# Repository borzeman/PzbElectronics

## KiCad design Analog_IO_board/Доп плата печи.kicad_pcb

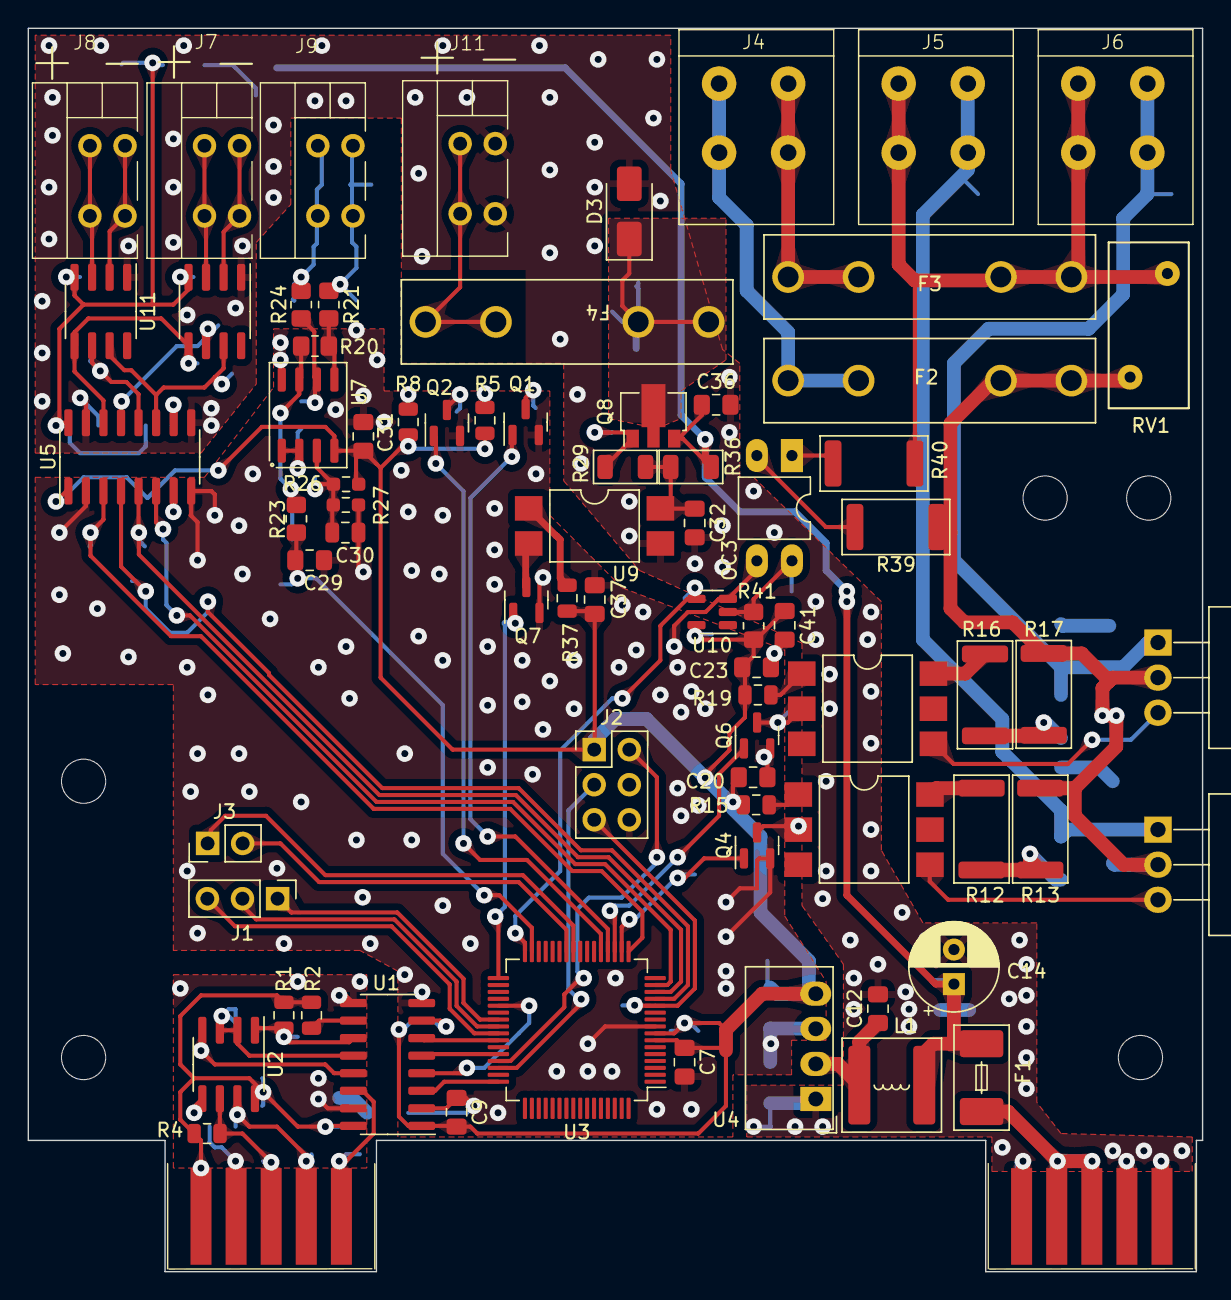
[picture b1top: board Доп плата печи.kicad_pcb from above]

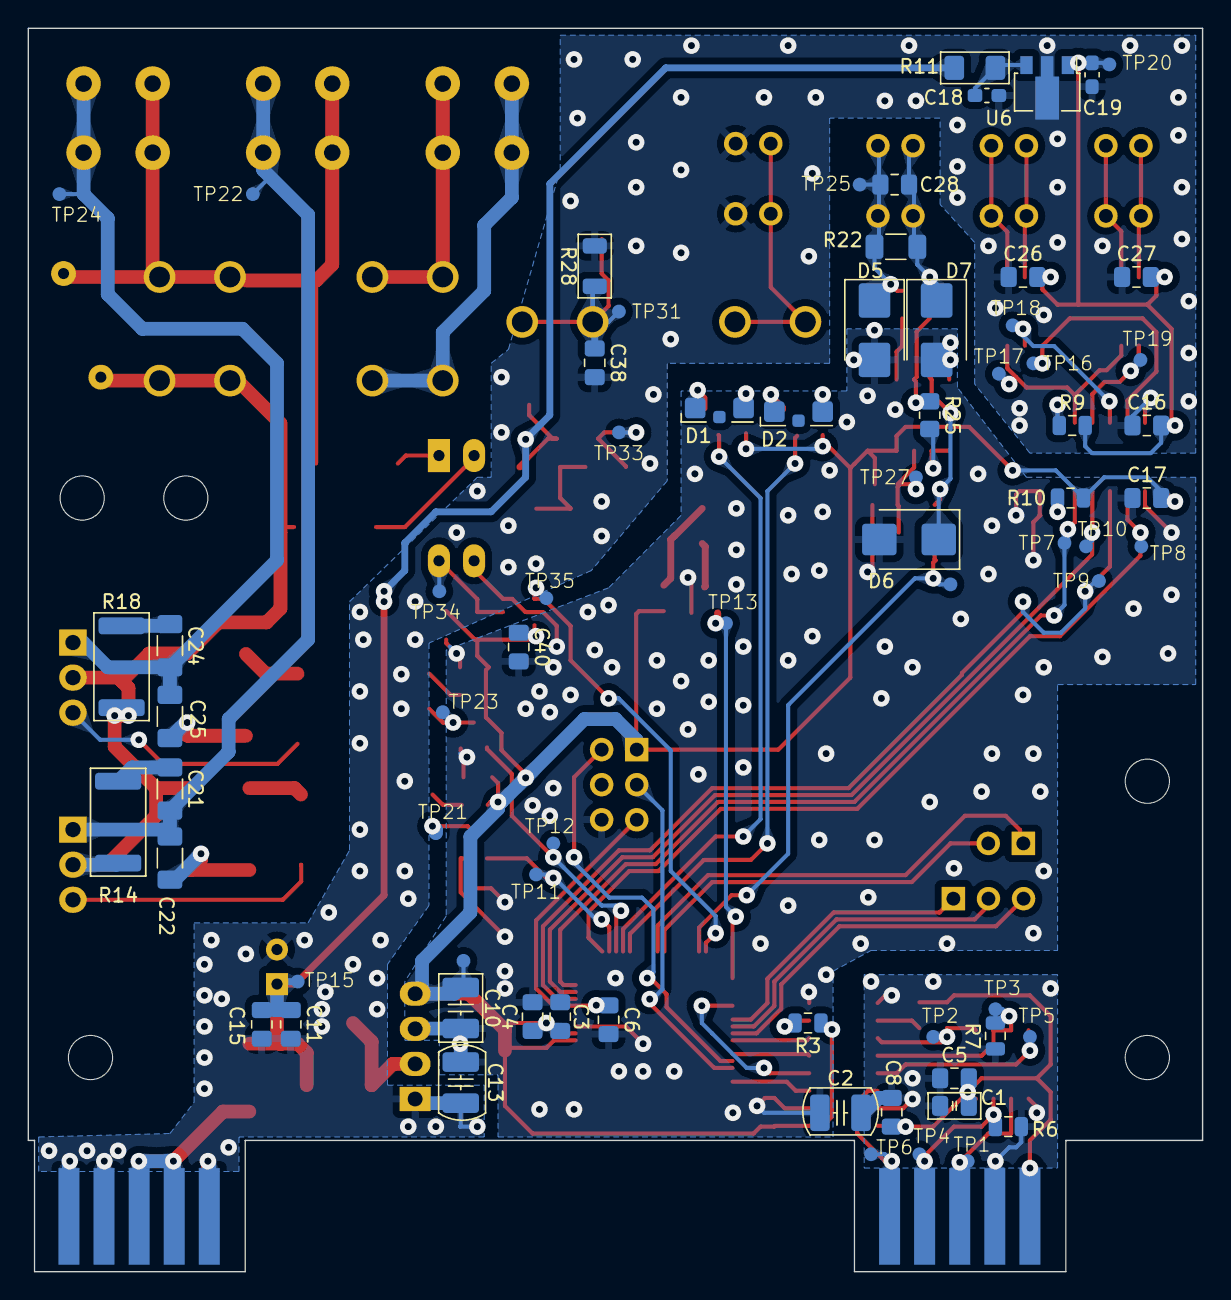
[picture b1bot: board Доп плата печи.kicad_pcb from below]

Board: 2 copper layers, 85.0 x 90.0 mm, 153 parts (72 on the bottom side), 89 nets.

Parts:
C1: 1uF 100V 0805; C_0805_2012Metric_Pad1.18x1.45mm_HandSolder
C2, C13: 270 pf X7R 1206 2000v 202R18W271KW4E; C_1210_3225Metric_Pad1.42x2.65mm
C3, C5, C6, C7, C8, C9, C15, C16, C17, C20, C23, C26, C27, C29, C32, C36, C37, C38: 0,1uF 100V 0805; C_0805_2012Metric_Pad1.18x1.45mm_HandSolder
C4, C11, C12: 4,7uF 50V 0805; C_0805_2012Metric_Pad1.18x1.45mm_HandSolder
C10: 10uF 50V 1210 GRM32ER71H106K; C_1210_3225Metric_Pad1.42x2.65mm_HandSolder
C14: 47uF 63V D6.3 H11; CP_Radial_D6.3mm_P2.50mm
C18: 0,33uF 50V 0603; C_0603_1608Metric_Pad1.08x0.95mm_HandSolder
C19: 0,1uF 50V 0603; C_0603_1608Metric_Pad1.08x0.95mm_HandSolder
C21, C22, C24, C25: 0,01uF 600V 1206 (GRM31BR72J103KW01L); C_1206_3216Metric_Pad1.33x1.80mm_HandSolder
C28, C31: 1uF 50V 0805; C_0805_2012Metric_Pad1.18x1.45mm_HandSolder
C30: 10uF 16V 0805; C_0805_2012Metric
C40, C41: 0,1uF 50V 0805; C_0805_2012Metric_Pad1.18x1.45mm_HandSolder
D1, D2: KPA-3010CGCK; LED_Kingbright_KPA-3010_3x2x1mm
D3: STPS2H100A (D_SMA); D_SMA
D5, D6, D7: SMBJ3V3-E3/52 (D_SMB); D_SMB
F1: 045201.5MRL; Fuse_Littelfuse-NANO2-451_453
F2, F3: Fuse 5A ZH266 (2 клипсы); Fuseholder_100_series_5x20mm_D1,5
F4: Fuse 0,16A 5x20 and ZH266 (2 клипсы); Fuseholder_100_series_5x20mm_D1,5
H1, H2, H3, H4, H5: MountingHole; MountingHole_3.2mm_M3
J1: DebugUSART (PinHeader_01x03_P2.54mm); PinHeader_1x03_P2.54mm_Vertical
J2: Prog (PinHeader_2x03_P2.54mm); PinHeader_2x03_P2.54mm_Vertical
J3: Debug GPIO (PinHeader_01x02_P2.54mm); PinHeader_1x02_P2.54mm_Vertical
J4, J5, J6: DG245-5.0-02P
J7, J8, J9, J11: DG141R-02
L1: 6,8uH 3,5A ETQP3M6R8KVP; L_Bourns-SRN6028
OC1, OC2: MOC3023SM (SMDIP-6); SMDIP-6_W9.53mm
OC3: FOD814 (DIP-4); DIP-4_W7.62mm_LongPads
Q1, Q2, Q4, Q6, Q7: DTC114ECA (SOT-23); SOT-23
Q3, Q5: BT136X-800E TO-220; TO-220-3_Horizontal_TabDown
Q8: BCX53-16 (SOT-89-3); SOT-89-3
R1, R7: 0805-10 кОм±5%-0,125 Вт; R_0805_2012Metric
R2, R3, R9, R10: 0805-4,7 кОм±5%-0,125 Вт; R_0805_2012Metric
R4, R6: 0805-560 Ом±5%-0,125 Вт; R_0805_2012Metric
R5, R8: 0805-150 Ом±5%-0,125 Вт; R_0805_2012Metric
R11: 1206-620 Ом±5%-0,25 Вт; R_1206_3216Metric_Pad1.42x1.75mm_HandSolder
R12, R16: 2512-180 Ом±5%-1 Вт; R_2512_6332Metric
R13, R17: 2512-1 кОм±5%-1 Вт; R_2512_6332Metric
R14, R18: 2512-51 Ом±5%-1 Вт; R_2512_6332Metric
R15, R19, R37: 0805-200 Ом±5%-0,125 Вт; R_0805_2012Metric
R20, R21, R23, R24, R25: 0805-1 кОм±1%-0,125 Вт; R_0805_2012Metric_Pad1.20x1.40mm_HandSolder
R22: 1206-33 Ом±5%-0,25 Вт; R_1206_3216Metric_Pad1.30x1.75mm_HandSolder
R26, R27: 0603-1 кОм±1%-0,062 Вт; R_0603_1608Metric_Pad0.98x0.95mm_HandSolder
R28: 1206-10 кОм±5%-0,25 Вт; R_1206_3216Metric
R29, R36: 1206-20 кОм±5%-0,25 Вт; R_1206_3216Metric
R39, R40: 2512-51 кОм±5%-1 Вт; R_2512_6332Metric
R41: 0805-1 кОм±5%-0,125 Вт; R_0805_2012Metric_Pad1.20x1.40mm_HandSolder
RS1, RS2: SL-10 (L-KLS1-603C-10-S); Edge_Conn_KLS1-603-10
RV1: V10E250P; RV_Disc_D12mm_W5.8mm_P7.5mm
TP1, TP2, TP3, TP4, TP5, TP6, TP7, TP8, TP9, TP10, TP11, TP12, TP13, TP14, TP15, TP16, TP17, TP18, TP19, TP20, TP21, TP22, TP23, TP24, TP25, TP26, TP27, TP31, TP33, TP34, TP35: TestPoint; TestPoint_D1
U1, U5: PAI141M30 (SOIC-16); SOIC-16_3.9x9.9mm_P1.27mm
U2: ADM3485EARZ-REEL (SOIC-8); SOIC-8_3.9x4.9mm_P1.27mm
U3: STM32G070RBTx (LQFP-64); LQFP-64_10x10mm_P0.5mm
U4: AM1SS-2403SJZ; Converter_DCDC_Murata_MEE1SxxxxSC_THT
U6: L78L33 (SOT89); SOT-89-3
U7: LMV358IDT (SO-8); SO-8_3.9x4.9mm_P1.27mm
U8, U11: MAX31855KASA (SOIC-8); SOIC-8_3.9x4.9mm_P1.27mm
U9: LTV-817S-(С-D) (SMDIP-4); SMDIP-4_W9.53mm
U10: 74AHCT1G14GW,125 (SOT-23-5); SOT-23-5

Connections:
+3.3VA: C16.2, C19.1, C26.2, C27.2, R9.2, TP20.1, U5.16 (VDD2), U6.1 (OUT), U8.4 (V_CC), U11.4 (V_CC)
+3V3: C3.1, C4.1, C7.1, C9.2, C10.1, C17.2, C20.1, C23.1, C31.1, C37.1, C40.1, C41.1, J2.1, R3.1, R5.2, R8.1, R10.1, R15.1, R19.1, R26.1, R37.1, R41.2, TP14.1, U1.1 (VDD1), U3.7 (VREF+), U3.8 (VDD), U4.4 (OUT+), U5.1 (VDD1), U7.4 (V-), U10.5 (VCC)
+24V: C11.1, C14.1, C15.1, C36.1, F1.2, L1.1, Q8.3 (E), R11.2, R36.2, TP15.1
/+3.3VRS485: C1.2, C5.2, C8.2, R1.2, R2.2, R4.2, RS1.1, RS1.10, U1.16 (VDD2), U2.8 (VCC)
/AddSchems/ACIN_1: F2.2, Q3.2 (A2), Q5.2 (A2), R13.1, R14.2, R17.1, R18.2, R39.1, RV1.1
/AddSchems/ACIN_2: F3.1, J5.1, J6.1, R40.2, RV1.2
/AddSchems/ACOUT1: C21.2, C22.2, J5.2, Q3.1 (A1), TP22.1
/AddSchems/ACOUT2: C24.2, C25.2, J6.2, Q5.1 (A1), TP24.1
/AddSchems/CLK_out: TP16.1, U5.14 (VOA), U8.5 (SCK), U11.5 (SCK)
/AddSchems/CS1_out: TP18.1, U5.13 (VOB), U8.6 (~CS)
/AddSchems/CS2_out: TP19.1, U5.12 (VOC), U11.6 (~CS)
/AddSchems/MISO_out: TP17.1, U5.11 (VID), U8.7 (SO), U11.7 (SO)
/CLK: TP8.1, U3.17 (PA0), U5.3 (VIA)
/CS1: TP9.1, U3.13 (PC0), U5.4 (VIB)
/CS2: TP10.1, U3.14 (PC1), U5.5 (VIC)
/DE_USART_1: U1.5 (VIC), U3.44 (PA12/PA10)
/Detect_zero: TP35.1, U3.32 (PB12), U10.4
/GPIO1: J3.1, U3.25 (PC4)
/GPIO2: J3.2, U3.26 (PC5)
/MISO: TP7.1, U3.15 (PC2), U5.6 (VOD)
/NRST: C6.1, J2.5, U3.12 (NRST)
/RTS: RS1.5, RS1.6, TP6.1, U1.14 (VOA)
/RTS_cont: U1.3 (VIA), U3.48 (PC8)
/RX_USART_1: U1.6 (VOD), U3.42 (PA10/NC)
/Relay_ON: Q7.1 (B), TP13.1, U3.33 (PB13)
/SIM1_ON: Q4.1 (B), TP11.1, U3.18 (PA1)
/SIM2_ON: Q6.1 (B), TP12.1, U3.19 (PA2)
/SWCLK: J2.3, U3.46 (PA14)
/SWDIO: J2.2, U3.45 (PA13)
/TX_USART_1: U1.4 (VIB), U3.37 (PA9/NC)
/UART_DE: J1.1, U3.39 (PC7)
/UART_RX: J1.3, U3.41 (PD9)
/UART_TX: J1.2, U3.40 (PD8)
/U_Idet1: C29.1, R23.2, TP26.1, U3.31 (PB11)
GND1: C1.1, C2.1, C5.1, C8.1, R6.1, R7.1, RS1.2, RS1.9, U1.9 (GND2), U1.15 (GND2), U2.5 (GND)
GNDA: C11.2, C12.2, C13.1, C14.2, C15.2, C16.1, C18.2, C19.2, C26.1, C27.1, C32.2, C36.2, C38.2, D3.2 (A), J11.1, R28.2, RS2.1, RS2.4, RS2.5, RS2.6, RS2.7, RS2.10, U4.1 (IN-), U5.9 (GND2), U5.15 (GND2), U6.2 (GND), U8.1 (GND), U9.3, U11.1 (GND)
GNDD: C2.2, C3.2, C4.2, C6.2, C7.2, C9.1, C10.2, C13.2, C17.1, C20.2, C23.2, C29.2, C30.2, C31.2, C37.2, C40.2, C41.2, D5.2 (A), D6.2 (A), D7.2 (A), J2.6, OC3.3, Q1.2 (E), Q2.2 (E), Q4.2 (E), Q6.2 (E), Q7.2 (E), R27.2, U1.2 (GND1), U1.8 (GND1), U3.9 (VSS), U4.3 (OUT-), U5.2 (GND1), U5.8 (GND1), U7.8 (V+), U10.3 (GND)
unnamed: C21.1, R14.1
unnamed: C22.1, R12.1, R13.2
unnamed: C24.1, R18.1
unnamed: C25.1, R16.1, R17.2
unnamed: C32.1, R29.1, R36.1, U9.4
unnamed: D1.2 (A), R5.1
unnamed: D1.1 (K), Q1.3 (C)
unnamed: D2.2 (A), R8.2
unnamed: D2.1 (K), Q2.3 (C)
unnamed: C38.1, D3.1 (K), F4.1, Q8.2 (C), R28.1, TP31.1
unnamed: C28.1, D5.1 (K), J9.1, R21.1, R22.1, TP25.1
unnamed: D6.1 (K), R20.2, R23.1, U7.7
unnamed: C28.2, D7.1 (K), J9.2, R22.2, R24.1
unnamed: F2.1, J4.1
unnamed: F3.2, J4.2
unnamed: J7.1, U8.2 (T-)
unnamed: J7.2, U8.3 (T+)
unnamed: J8.1, U11.2 (T-)
unnamed: J8.2, U11.3 (T+)
unnamed: F4.2, J11.2
unnamed: OC1.1, R15.2
unnamed: OC1.6, R12.2
unnamed: OC2.1, R19.2
unnamed: OC2.6, R16.2
unnamed: OC3.1, R40.1
unnamed: OC3.2, R39.2
unnamed: OC3.4, R41.1, TP34.1, U10.2
unnamed: Q1.1 (B), U3.20 (PA3)
unnamed: Q2.1 (B), U3.21 (PA4)
unnamed: OC1.4, Q3.3 (G)
unnamed: OC1.2, Q4.3 (C), TP21.1
unnamed: OC2.4, Q5.3 (G)
unnamed: OC2.2, Q6.3 (C), TP23.1
unnamed: Q7.3 (C), U9.2
unnamed: Q8.1 (B), R29.2, TP33.1
unnamed: R37.2, U9.1
unnamed: R4.1, RS1.3, RS1.8, TP1.1, U2.6 (A)
unnamed: R6.2, RS1.4, RS1.7, TP4.1, U2.7 (B)
unnamed: F1.1, RS2.2, RS2.3, RS2.8, RS2.9
unnamed: R3.2, U1.7 (VE1)
unnamed: R2.1, U1.10 (VE2)
unnamed: R1.1, TP2.1, U1.11 (VID), U2.1 (RO)
unnamed: TP5.1, U1.13 (VOB), U2.4 (DI)
unnamed: R7.2, TP3.1, U1.12 (VOC), U2.2 (~RE), U2.3 (DE)
unnamed: C12.1, L1.2, U4.2 (IN+)
unnamed: R10.2, U5.7 (VE1)
unnamed: R9.1, U5.10 (VE2)
unnamed: C18.1, R11.1, U6.3 (IN)
unnamed: C30.1, R26.2, R27.1, TP27.1, U7.3 (+)
unnamed: R25.2, U7.1, U7.2 (-)
unnamed: R20.1, R21.2, U7.5 (+)
unnamed: R24.2, R25.1, U7.6 (-)

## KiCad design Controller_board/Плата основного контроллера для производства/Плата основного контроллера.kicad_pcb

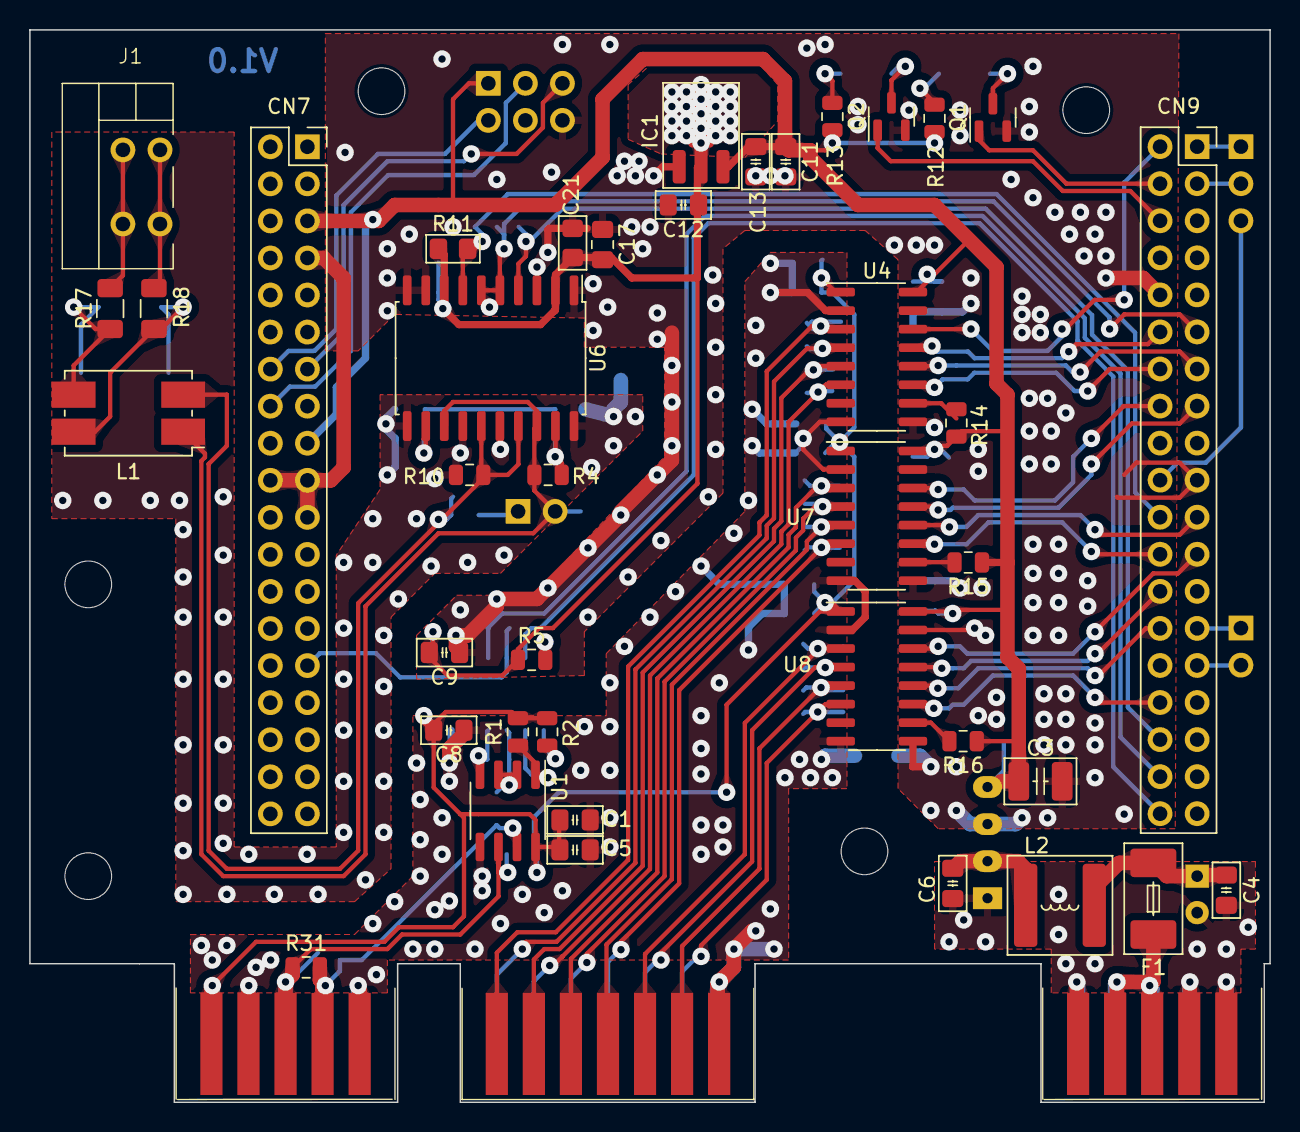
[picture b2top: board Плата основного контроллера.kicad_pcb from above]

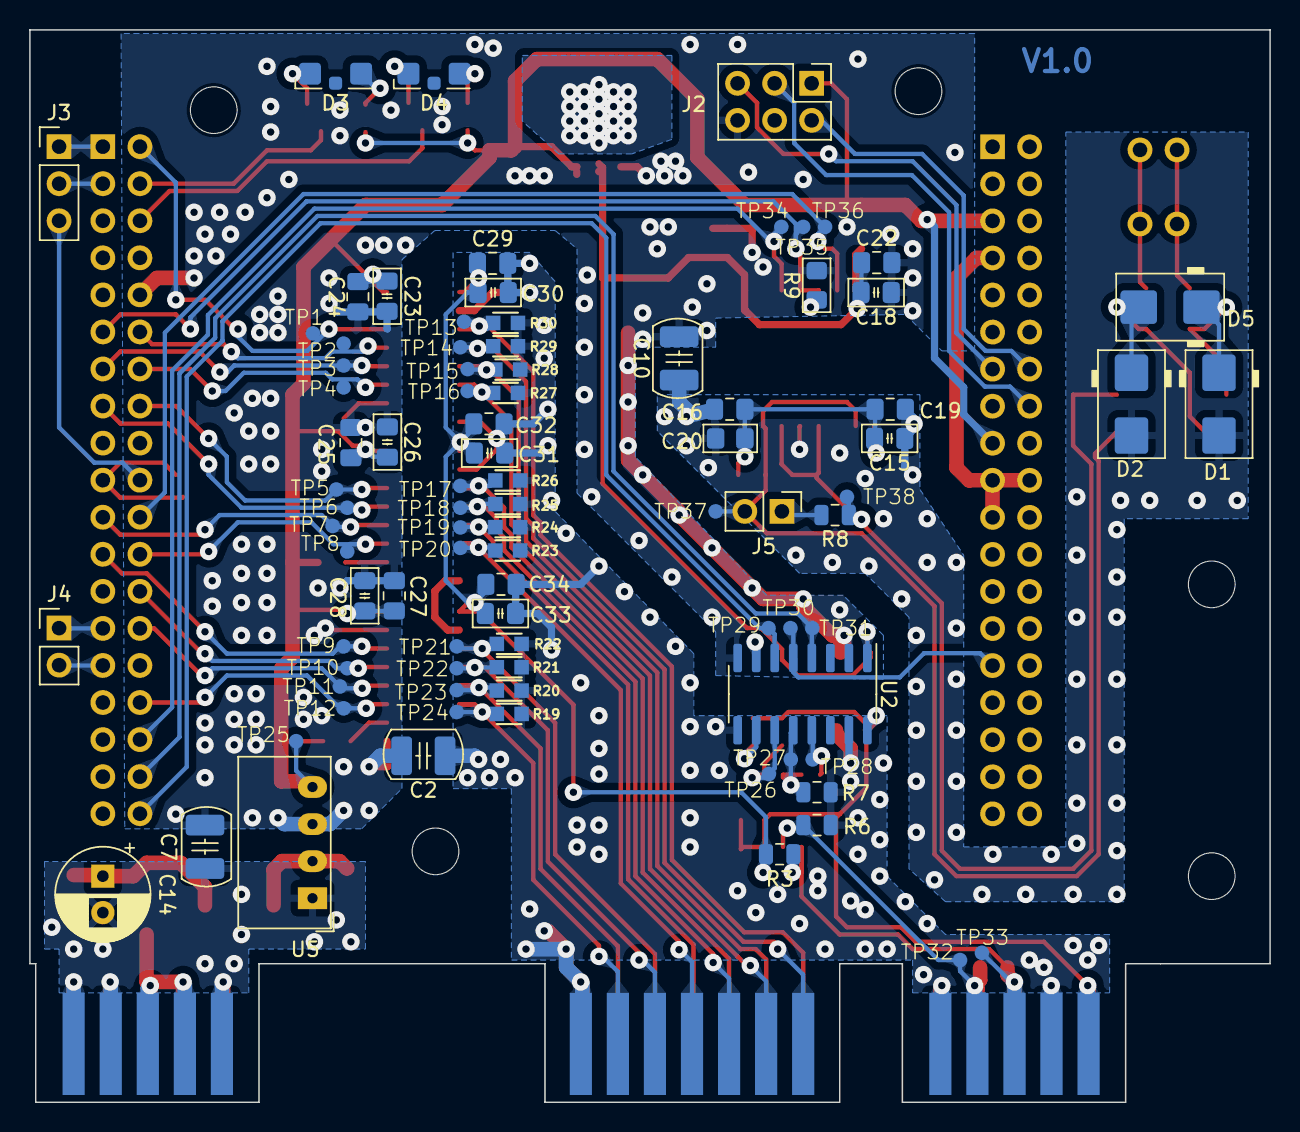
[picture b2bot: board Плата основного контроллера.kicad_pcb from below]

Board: 2 copper layers, 85.0 x 73.5 mm, 136 parts (88 on the bottom side), 72 nets.

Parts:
C1, C11: 1uF 50V 0805; C_0805_2012Metric_Pad1.18x1.45mm_HandSolder
C2, C7, C10: 270 pf X7R 1206 2000v 202R18W271KW4E; C_1210_3225Metric_Pad1.42x2.65mm
C3: 10uF 50V 1210 GRM32ER71H106K; C_1210_3225Metric_Pad1.42x2.65mm_HandSolder
C4, C6: 4,7uF 50V 0805; C_0805_2012Metric_Pad1.18x1.45mm_HandSolder
C5, C8, C9, C13, C16, C17, C19, C22, C24, C25, C27, C29, C32, C34: 0,1uF 50V 0805; C_0805_2012Metric_Pad1.18x1.45mm_HandSolder
C12, C15, C18, C23, C26, C28, C30, C31, C33: 10uF 16V 0805; C_0805_2012Metric_Pad1.18x1.45mm_HandSolder
C14: 47uF 63V D10,5; CP_Radial_D6.3mm_P2.50mm
C20, C21: 10nF 50V 0805; R_0805_2012Metric_Pad1.20x1.40mm_HandSolder
CN7, CN9: DS1023-2x19S21; PinSocket_2x19_P2.54mm_Vertical
D1, D2: SMBJ5.0A; D_SMB
D3, D4: KPA-3010CGCK; LED_Kingbright_KPA-3010_3x2x1mm
D5: SMBJ10CA; D_SMB
F1: 0452.500MRL; Fuse_Littelfuse-NANO2-451_453
H1, H2, H3, H4, H5: MountingHole; MountingHole_3.2mm_M3
IC1: LD1117-3.3V-SOT223; SOT-89-3_BigPads
J1: DG141R-02 (RS485); DG141R-02
J2: Prog (PinHeader_2x03_P2.54mm); PinHeader_2x03_P2.54mm_Vertical
J3: DebugUSART (PinHeader_01x03_P2.54mm); PinHeader_1x03_P2.54mm_Vertical
J4: Debug GPIO (PinHeader_01x02_P2.54mm); PinHeader_1x02_P2.54mm_Vertical
J5: DS1027-2B и PinHeader_2x01_P2.54mm; PinHeader_1x02_P2.54mm_Vertical
L1: B82790S0253N201; L_CommonMode_Delevan_4222
L2: 6,8uH 3,5A (ETQP3M6R8KVP); L_Bourns-SRN6028
Q1, Q2: DTC114ECA (SOT-23); SOT-23
R1, R7: 0805-10 кОм±5%-0,125 Вт; R_0805_2012Metric
R2, R5: 0805-4,7 кОм±5%-0,125 Вт; R_0805_2012Metric
R3, R4, R6, R10: 0805-560 Ом±5%-0,125 Вт; R_0805_2012Metric
R8, R31: 0805 -120 Ом±5%-0,125 Вт; R_0805_2012Metric
R9, R11: 0805-10 кОм±5%-0,125 Вт; R_0805_2012Metric_Pad1.20x1.40mm_HandSolder
R12, R13: 0805-300 Ом±5%-0,125 Вт; R_0805_2012Metric
R14, R15, R16: 0805-100 Ом±5%-0,125 Вт; R_0805_2012Metric
R17, R18: 1206-100 Ом±5%-0,25 Вт; R_1206_3216Metric
R19, R20, R21, R22, R23, R24, R25, R26, R27, R28, R29, R30: 0603-10 кОм±5%-0,062 Вт; R_0603
RS1, RS2: SL-10 (L-KLS1-603C-10-S); Edge_Conn_KLS1-603-10
RS3: SL-14 (L-KLS1-603C-14-S) RTS; Edge_Conn_KLS1-603-14
TP1, TP2, TP3, TP4, TP5, TP6, TP7, TP8, TP9, TP10, TP11, TP12, TP13, TP14, TP15, TP16, TP17, TP18, TP19, TP20, TP21, TP22, TP23, TP24, TP25, TP26, TP27, TP28, TP29, TP30, TP31, TP32, TP33, TP34, TP35, TP36, TP37, TP38: TestPoint; TestPoint_D1
U1: ADM3485EARZ-REEL (SOIC-8); SOIC-8_3.9x4.9mm_P1.27mm
U2: pia141M30 (SOIC-16); SOIC-16_3.9x9.9mm_P1.27mm
U4, U7, U8: pia140M30 (SOIC-16); SOIC-16_3.9x9.9mm_P1.27mm
U5: SMU02N-05; Converter_DCDC_Murata_CRE1xxxxxxSC_THT
U6: ADM2587E (SOIC-20); SOIC-20W_7.5x12.8mm_P1.27mm

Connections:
+3V3: C9.2, C12.1, C17.2, C18.2, C21.2, C22.1, IC1.2 (OUT), R5.1, R11.1, U2.1 (VDD1), U6.2 (VCC), U6.8 (VCC)
+5V: C3.1, C11.1, C13.1, C23.2, C24.1, C25.1, C26.2, C27.1, C28.2, CN7.5, CN7.17, IC1.3 (IN), J2.1, R12.2, R13.1, R14.1, R15.1, R16.1, TP25.1, U4.16 (VDD2), U5.4 (OUT+), U7.16 (VDD2), U8.16 (VDD2)
+24V: C4.1, C14.1, F1.2, L2.1
/+3.3VRS485: C1.2, C5.2, C8.2, C29.1, C30.2, C31.2, C32.1, C33.2, C34.1, R1.2, R2.2, R3.2, RS1.1, RS1.10, U1.8 (VCC), U2.16 (VDD2), U4.1 (VDD1), U7.1 (VDD1), U8.1 (VDD1)
/GPIO1: CN9.27, J4.1
/GPIO2: CN9.29, J4.2
/LED1: CN9.4, Q1.1 (B)
/LED2: CN9.6, Q2.1 (B)
/NUCLEO-64F411/RESET: CN7.13, J2.5
/NUCLEO-64F411/SWCLK: CN7.16, J2.3
/NUCLEO-64F411/SWDIO: CN7.14, J2.2
/RTS1: R30.1, RS3.1, TP13.1, U4.3 (VIA)
/RTS1_cont: CN9.2, TP1.1, U4.14 (VOA)
/RTS2: R29.1, RS3.14, TP14.1, U4.4 (VIB)
/RTS2_cont: CN9.12, TP2.1, U4.13 (VOB)
/RTS3: R28.1, RS3.2, TP15.1, U4.5 (VIC)
/RTS3_cont: CN9.13, TP3.1, U4.12 (VOC)
/RTS4: R27.1, RS3.13, TP16.1, U4.6 (VID)
/RTS4_cont: CN9.14, TP4.1, U4.11 (VOD)
/RTS5: R26.1, RS3.3, TP17.1, U7.3 (VIA)
/RTS5_cont: CN9.16, TP5.1, U7.14 (VOA)
/RTS6: R25.1, RS3.12, TP18.1, U7.4 (VIB)
/RTS6_cont: CN9.15, TP6.1, U7.13 (VOB)
/RTS7: R24.1, RS3.4, TP19.1, U7.5 (VIC)
/RTS7_cont: CN9.21, TP7.1, U7.12 (VOC)
/RTS8: R23.1, RS3.11, TP20.1, U7.6 (VID)
/RTS8_cont: CN9.24, TP8.1, U7.11 (VOD)
/RTS9: R22.1, RS3.5, TP21.1, U8.3 (VIA)
/RTS9_cont: CN9.23, TP9.1, U8.14 (VOA)
/RTS10: R21.1, RS3.10, TP22.1, U8.4 (VIB)
/RTS10_cont: CN9.26, TP10.1, U8.13 (VOB)
/RTS11: R20.1, RS3.6, TP23.1, U8.5 (VIC)
/RTS11_cont: CN9.28, TP11.1, U8.12 (VOC)
/RTS12: R19.1, RS3.9, TP24.1, U8.6 (VID)
/RTS12_cont: CN9.32, TP12.1, U8.11 (VOD)
/UART6_DE: CN9.1, J3.1
/USART1_RTS: CN9.11, R9.1, TP35.1, U6.5 (~RE), U6.6 (DE)
/USART1_RX: CN9.34, TP34.1, U6.4 (RxD)
/USART1_TX: CN9.22, R11.2, TP36.1, U6.7 (TxD)
/USART2_RTS: CN7.29, TP30.1, U2.5 (VIC)
/USART2_RX: CN9.38, TP29.1, U2.6 (VOD)
/USART2_TX: CN9.36, TP31.1, U2.4 (VIB)
/USART6_RX: CN9.20, J3.3
/USART6_TX: CN9.3, J3.2
GND1: C1.1, C2.1, C5.1, C8.1, C29.2, C30.1, C31.1, C32.2, C33.1, C34.2, R6.1, R7.1, R19.2, R20.2, R21.2, R22.2, R23.2, R24.2, R25.2, R26.2, R27.2, R28.2, R29.2, R30.2, RS1.2, RS1.5, RS1.6, RS1.9, RS3.7, RS3.8, U1.5 (GND), U2.9 (GND2), U2.15 (GND2), U4.2 (GND1), U4.8 (GND1), U7.2 (GND1), U7.8 (GND1), U8.2 (GND1), U8.8 (GND1)
GND2: C10.2, C15.1, C16.1, C19.1, C20.1, D1.2 (A), D2.2 (A), R10.1, U6.11 (GND2), U6.14 (GND2), U6.16 (GND2), U6.20 (GND2)
GNDA: C4.2, C6.2, C7.1, C14.2, RS2.1, RS2.4, RS2.5, RS2.6, RS2.7, RS2.10, U5.1 (IN-)
GNDD: C2.2, C3.2, C7.2, C9.1, C10.1, C11.2, C12.2, C13.2, C17.1, C18.1, C21.1, C22.2, C23.1, C24.2, C25.2, C26.1, C27.2, C28.1, CN7.7, CN7.19, CN7.20, CN7.21, CN9.10, CN9.19, IC1.1 (ADJ), J2.6, Q1.2 (E), Q2.2 (E), R9.2, U2.2 (GND1), U2.8 (GND1), U4.9 (GND2), U4.15 (GND2), U5.3 (OUT-), U6.1 (GND1), U6.3 (GND1), U6.9 (GND1), U6.10 (GND1), U7.9 (GND2), U7.15 (GND2), U8.9 (GND2), U8.15 (GND2)
unnamed: D1.1 (K), D5.1 (K), L1.3, R18.2
unnamed: D2.1 (K), D5.2 (A), L1.4, R17.1
unnamed: D3.2 (A), R12.1
unnamed: D3.1 (K), Q1.3 (C)
unnamed: D4.2 (A), R13.2
unnamed: D4.1 (K), Q2.3 (C)
unnamed: J1.1, R17.2
unnamed: J1.2, R18.1
unnamed: J5.1, R8.2
unnamed: J5.2, L1.1, R4.2, TP37.1, U6.13 (Y), U6.18 (A)
unnamed: R3.1, R31.2, RS1.3, RS1.8, TP33.1, U1.6 (A)
unnamed: R6.2, R31.1, RS1.4, RS1.7, TP32.1, U1.7 (B)
unnamed: F1.1, RS2.2, RS2.3, RS2.8, RS2.9
unnamed: R7.2, TP27.1, U1.2 (~RE), U1.3 (DE), U2.12 (VOC)
unnamed: TP28.1, U1.4 (DI), U2.13 (VOB)
unnamed: R1.1, TP26.1, U1.1 (RO), U2.11 (VID)
unnamed: R5.2, U2.7 (VE1)
unnamed: R2.1, U2.10 (VE2)
unnamed: R14.2, U4.10 (VE2)
unnamed: C6.1, L2.2, U5.2 (IN+)
unnamed: L1.2, R8.1, R10.2, TP38.1, U6.15 (Z), U6.17 (B)
unnamed: C15.2, C16.2, C19.2, C20.2, R4.1, U6.12 (Visoout), U6.19 (Visoin)
unnamed: R15.2, U7.10 (VE2)
unnamed: R16.2, U8.10 (VE2)

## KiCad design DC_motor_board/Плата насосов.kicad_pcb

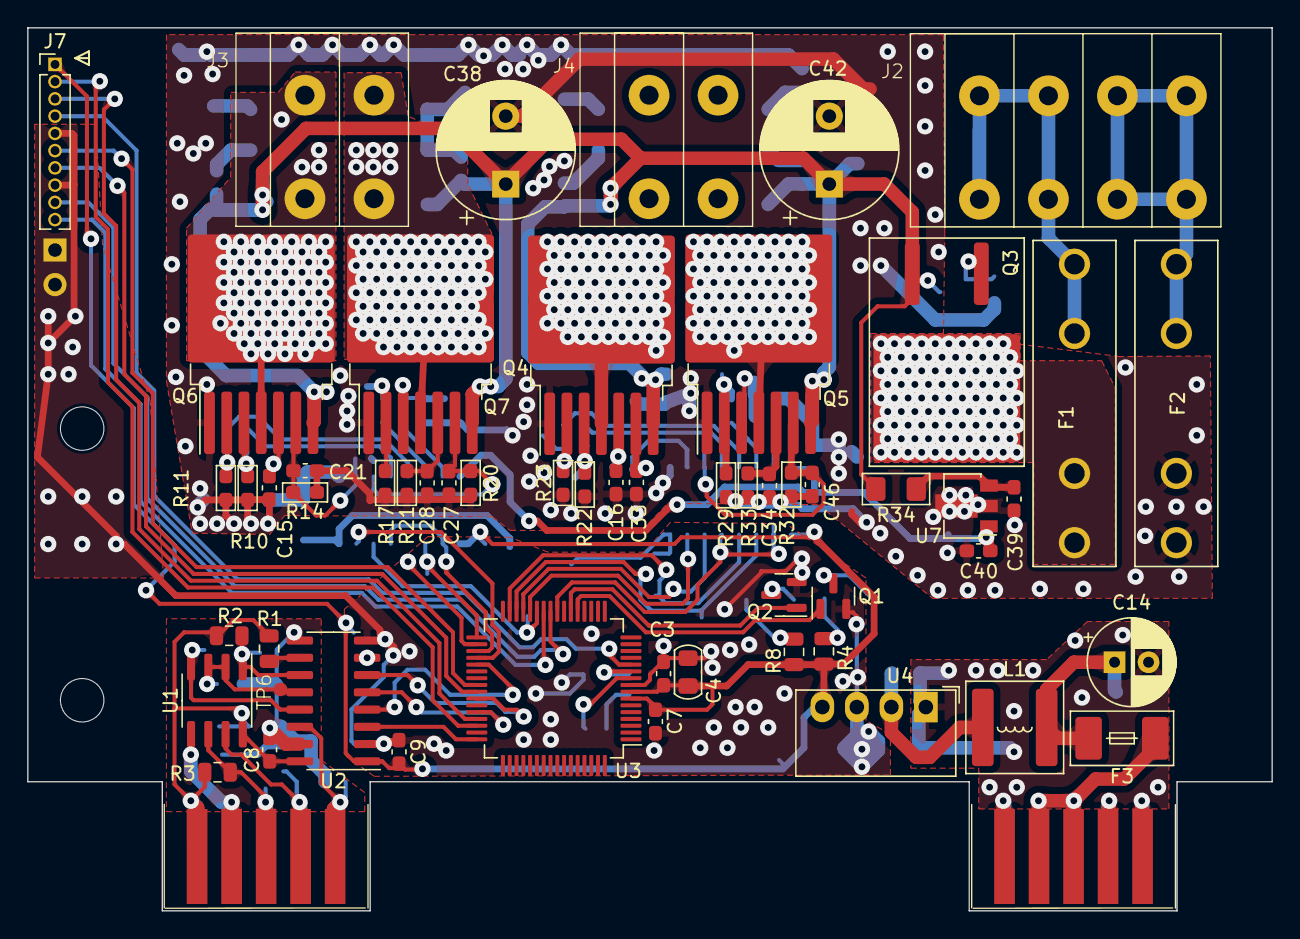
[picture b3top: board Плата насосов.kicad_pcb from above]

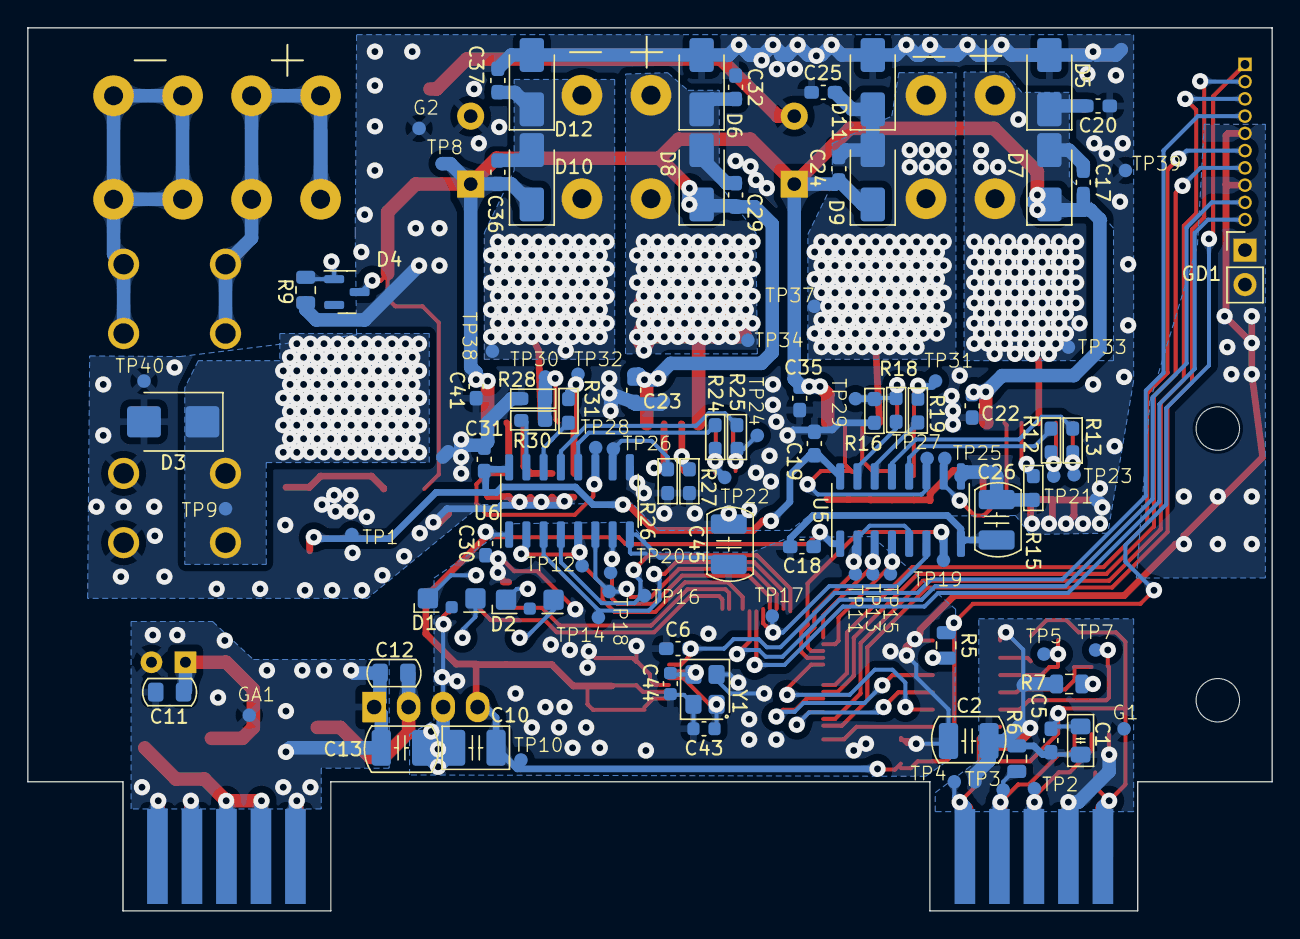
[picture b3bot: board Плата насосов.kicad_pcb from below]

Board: 2 copper layers, 91.6 x 65.0 mm, 161 parts (101 on the bottom side), 81 nets.

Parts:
C1: 1uF 100V 0805; C_0805_2012Metric_Pad1.18x1.45mm_HandSolder
C2, C13, C26, C45: 270 pf X7R 1206 2000v 202R18W271KW4E; C_1210_3225Metric_Pad1.42x2.65mm
C3, C5, C6, C7, C8, C9, C15, C16, C18, C19, C22, C23, C28, C30, C31, C34, C35, C40, C41: 0,1uF 100V 0603; C_0603_1608Metric_Pad1.08x0.95mm_HandSolder
C4, C11, C12: 4,7uF 50V 0805; C_0805_2012Metric_Pad1.15x1.40mm
C10: 10uF 50V 1210 GRM32ER71H106K; C_1210_3225Metric_Pad1.42x2.65mm_HandSolder
C14: 47uF 63V D6.3 H11; CP_Radial_D6.3mm_P2.50mm
C17, C20, C24, C25, C29, C32, C36, C37: 0,22uF 100V 0603; C_0603_1608Metric_Pad1.08x0.95mm_HandSolder
C21, C27, C33, C46: 1nF 50V 0603; C_0603_1608Metric_Pad1.08x0.95mm_HandSolder
C38, C42: 330uF 50V D10 H17; CP_Radial_D10.0mm_P5.00mm
C39: 0,33uF 50V 0603; C_0603_1608Metric_Pad1.08x0.95mm_HandSolder
C43, C44: 20pF 50V 0603; C_0603_1608Metric
D1, D2: KPA-3010CGCK; LED_Kingbright_KPA-3010_3x2x1mm
D3: SM6T30СA (SMB); D_SMB
D4: BZX84C10 (SOT-23); SOT-23
D5, D6, D7, D8, D9, D10, D11, D12: STPS2H100A; D_SMA
F1, F2: Fuse 5A ZH266 (2 клипсы); Fuseholder_100_series_5x20mm_D1,5
F3: 0452.500MRL; Fuse_Littelfuse-NANO2-451_453
G1, G2: TestPoint; TestPoint_D1
GA1: TestPoint; TestPoint_D1
GD1: PLS-2; PinHeader_1x02_P2.54mm_Vertical
H1, H2: MountingHole; MountingHole_3.2mm_M3
J2: DG142R-5.08-04P-14 IN24V; DG142R-5.08-04P-14
J3, J4: DG142R-5.08-02P-14 OUT; DG142R-5.08-02P-14
J7: PLL-10; PinHeader_1x10_P1.27mm_Vertical
L1: 6,8uH 3,5A ETQP3M6R8KVP; L_Bourns-SRN6028
Q1, Q2: DTC114ECA (SOT-23); SOT-23
Q3: IRF4905SPbF (D2PAK); TO-263-2
Q4, Q5, Q6, Q7: BTN8962TA (TO-263-7); TO-263-7_TabPin8
R1, R5: 0805-4,7 кОм±5%-0,125 Вт; R_0805_2012Metric
R2, R7, R9: 0805-10 кОм±5%-0,125 Вт; R_0805_2012Metric
R3, R6: 0805-560 Ом±5%-0,125 Вт; R_0805_2012Metric
R4, R8: 0805-150 Ом±5%-0,125 Вт; R_0805_2012Metric
R10, R11, R16, R17, R22, R23, R28, R29: 0603-100 кОм±5%-0,062 Вт; R_0603_1608Metric_Pad1.05x0.95mm_HandSolder
R12, R13, R18, R19, R24, R25, R30, R31: 0603-10 кОм±5%-0,062 Вт; R_0603_1608Metric_Pad1.05x0.95mm_HandSolder
R14, R15, R20, R21, R26, R27, R32, R33: 0603-1 кОм±5%-0,062 Вт; R_0603_1608Metric_Pad1.05x0.95mm_HandSolder
R34: 1206-620 Ом±5%-0,25 Вт; R_1206_3216Metric_Pad1.42x1.75mm_HandSolder
RS1, RS2: SL-10 (L-KLS1-603C-10-S); Edge_Conn_KLS1-603-10
TP1, TP2, TP3, TP4, TP5, TP6, TP7, TP8, TP9, TP10, TP11, TP12, TP13, TP14, TP15, TP16, TP17, TP18, TP19, TP20, TP21, TP22, TP23, TP24, TP25, TP26, TP27, TP28, TP29, TP30, TP31, TP32, TP33, TP34, TP37, TP38, TP39, TP40: TestPoint; TestPoint_D1
U1: ADM3485EARZ-REEL (SOIC-8); SOIC-8_3.9x4.9mm_P1.27mm
U2: PAI141M30 (SOIC-16); SOIC-16_3.9x9.9mm_P1.27mm
U3: STM32G070RBTx (LQFP-64); LQFP-64_10x10mm_P0.5mm
U4: AM1SS-2403SJZ; Converter_DCDC_Murata_MEE1SxxxxSC_THT
U5, U6: PAI162M30 (SOIC-16); SOIC-16_3.9x9.9mm_P1.27mm
U7: L78L05 (SOT89-3); SOT-89-3
Y1: Crystal_3225 8MHz; Crystal_SMD_3225-4Pin_3.2x2.5mm

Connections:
+3V3: C3.1, C4.1, C7.1, C9.2, C10.1, C18.2, C30.2, J7.1, R4.2, R5.1, R8.1, TP10.1, U2.1 (VDD1), U3.7 (VREF+), U3.8 (VDD), U4.4 (OUT+), U5.1 (VDD1), U6.1 (VDD1)
+24V: C11.1, C14.1, F3.2, L1.1
/+3.3VRS485: C1.2, C5.2, C8.2, R1.2, R2.2, R3.2, RS1.1, RS1.10, U1.8 (VCC), U2.16 (VDD2)
/+5V: C19.1, C31.1, C40.1, TP1.1, U5.16 (VDD2), U6.16 (VDD2), U7.1 (OUT)
/+24_INNER: C17.2, C22.1, C23.1, C24.2, C29.2, C35.1, C36.2, C38.1, C41.1, C42.1, D4.3 (K), D7.1 (K), D8.1 (K), D9.1 (K), D10.1 (K), Q3.3 (S), Q4.7, Q5.7, Q6.7, Q7.7, R34.2, TP8.1
/Back_1: TP16.1, U3.31 (PB11), U6.4 (VIC)
/Back_2: TP15.1, U3.34 (PB14), U5.4 (VIC)
/DE_USART_1: U2.5 (VIC), U3.44 (PA12/PA10)
/Enable_1: TP12.1, U3.24 (PA7), U6.2 (VIA), U6.5 (VID)
/Enable_2: TP11.1, U3.35 (PB15), U5.2 (VIA), U5.5 (VID)
/Forward_1: TP14.1, U3.30 (PB10), U6.3 (VIB)
/Forward_2: TP13.1, U3.33 (PB13), U5.3 (VIB)
/GPIO1: J7.9, U3.25 (PC4)
/GPIO2: J7.10, U3.26 (PC5)
/IS1_1: TP20.1, U3.28 (PB1), U6.7 (VOF)
/IS1_2: TP19.1, U3.36 (PA8), U5.7 (VOF)
/IS2_1: TP18.1, U3.29 (PB2), U6.6 (VOE)
/IS2_2: TP17.1, U3.27 (PB0), U5.6 (VOE)
/NRST: C6.1, J7.4, U3.12 (NRST)
/OSC_IN: C43.1, U3.10 (PF0), Y1.1
/OSC_OUT: C44.1, U3.11 (PF1), Y1.3
/RTS: RS1.5, RS1.6, TP4.1, U2.14 (VOA)
/RTS_cont: U2.3 (VIA), U3.48 (PC8)
/RX_USART_1: U2.6 (VOD), U3.42 (PA10/NC)
/SWCLK: J7.2, U3.46 (PA14)
/SWDIO: J7.3, U3.45 (PA13)
/TX_USART_1: U2.4 (VIB), U3.37 (PA9/NC)
/UART_RX: J7.7, U3.41 (PD9)
/UART_TX: J7.6, U3.40 (PD8)
GND1: C1.1, C2.1, C5.1, C8.1, G1.1, R6.1, R7.1, RS1.2, RS1.9, U1.5 (GND), U2.9 (GND2), U2.15 (GND2)
GND2: C15.1, C16.1, C19.2, C20.1, C21.1, C22.2, C23.2, C25.1, C26.2, C27.1, C28.1, C31.2, C32.1, C33.1, C34.1, C35.2, C37.1, C38.2, C39.2, C40.2, C41.2, C42.2, C45.2, C46.1, D3.2 (A2), D5.2 (A), D6.2 (A), D11.2 (A), D12.2 (A), F2.1, G2.1, Q4.1, Q5.1, Q6.1, Q7.1, R9.2, R10.2, R11.1, R14.1, R15.1, R16.2, R17.1, R20.1, R21.1, R22.2, R23.1, R26.1, R27.1, R28.2, R29.1, R32.1, R33.1, TP39.1, TP40.1, U5.9 (GND2), U6.9 (GND2), U7.2 (GND)
GNDA: C11.2, C12.2, C13.1, C14.2, GA1.1, RS2.1, RS2.4, RS2.5, RS2.6, RS2.7, RS2.10, U4.1 (IN-)
GNDD: C2.2, C3.2, C4.2, C6.2, C7.2, C9.1, C10.2, C13.2, C18.1, C26.1, C30.1, C43.2, C44.2, C45.1, GD1.1, GD1.2, J7.5, J7.8, Q1.2 (E), Q2.2 (E), U2.2 (GND1), U2.8 (GND1), U3.9 (VSS), U4.3 (OUT-), U5.8 (GND1), U6.8 (GND1), Y1.2, Y1.4
unnamed: D1.2 (A), R4.1
unnamed: D1.1 (K), Q1.3 (C)
unnamed: D2.2 (A), R8.2
unnamed: D2.1 (K), Q2.3 (C)
unnamed: D3.1 (A1), F1.1, Q3.2 (D), TP9.1
unnamed: D4.1 (A), Q3.1 (G), R9.1
unnamed: C17.1, C20.2, D5.1 (K), D7.2 (A), J3.1, Q6.4, Q6.8, TP33.1
unnamed: C29.1, C32.2, D6.1 (K), D8.2 (A), J4.1, Q4.4, Q4.8, TP34.1
unnamed: C36.1, C37.2, D10.2 (A), D12.1 (K), J4.2, Q5.4, Q5.8, TP38.1
unnamed: C24.1, C25.2, D9.2 (A), D11.1 (K), J3.2, Q7.4, Q7.8, TP37.1
unnamed: F1.2, J2.1, J2.2
unnamed: F2.2, J2.3, J2.4
unnamed: Q1.1 (B), U3.21 (PA4)
unnamed: Q2.1 (B), U3.22 (PA5)
unnamed: Q4.2 (IN), R23.2, R25.1, TP24.1
unnamed: Q4.3 (INH), R22.1, R24.2, TP22.1
unnamed: C33.2, Q4.6 (IS), R26.2, TP26.1, U6.10 (VIF)
unnamed: C16.2, Q4.5 (SR), R27.2
unnamed: Q5.2 (IN), R29.2, R31.1, TP32.1
unnamed: Q5.3 (INH), R28.1, R30.2, TP30.1
unnamed: C46.2, Q5.6 (IS), R32.2, TP28.1, U6.11 (VIE)
unnamed: C34.2, Q5.5 (SR), R33.2
unnamed: Q6.2 (IN), R11.2, R13.1, TP23.1
unnamed: Q6.3 (INH), R10.1, R12.2, TP21.1
unnamed: C21.2, Q6.6 (IS), R14.2, TP25.1, U5.10 (VIF)
unnamed: C15.2, Q6.5 (SR), R15.2
unnamed: Q7.2 (IN), R17.2, R19.1, TP31.1
unnamed: Q7.3 (INH), R16.1, R18.2, TP29.1
unnamed: C27.2, Q7.6 (IS), R20.2, TP27.1, U5.11 (VIE)
unnamed: C28.2, Q7.5 (SR), R21.2
unnamed: R3.1, RS1.3, RS1.8, TP2.1, U1.6 (A)
unnamed: R6.2, RS1.4, RS1.7, TP3.1, U1.7 (B)
unnamed: F3.1, RS2.2, RS2.3, RS2.8, RS2.9
unnamed: R7.2, TP6.1, U1.2 (~RE), U1.3 (DE), U2.12 (VOC)
unnamed: TP7.1, U1.4 (DI), U2.13 (VOB)
unnamed: R2.1, TP5.1, U1.1 (RO), U2.11 (VID)
unnamed: R5.2, U2.7 (VE1)
unnamed: R1.1, U2.10 (VE2)
unnamed: C12.1, L1.2, U4.2 (IN+)
unnamed: R18.1, U5.15 (VOA)
unnamed: R19.2, U5.14 (VOB)
unnamed: R13.2, U5.13 (VOC)
unnamed: R12.1, U5.12 (VOD)
unnamed: R30.1, U6.15 (VOA)
unnamed: R31.2, U6.14 (VOB)
unnamed: R25.2, U6.13 (VOC)
unnamed: R24.1, U6.12 (VOD)
unnamed: C39.1, R34.1, U7.3 (IN)
